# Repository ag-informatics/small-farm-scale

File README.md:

# Welcome to your organization's demo respository
This code repository (or "repo") is designed to demonstrate the best GitHub has to offer with the least amount of noise.

The repo includes an `index.html` file (so it can render a web page), two GitHub Actions workflows, and a CSS stylesheet dependency.

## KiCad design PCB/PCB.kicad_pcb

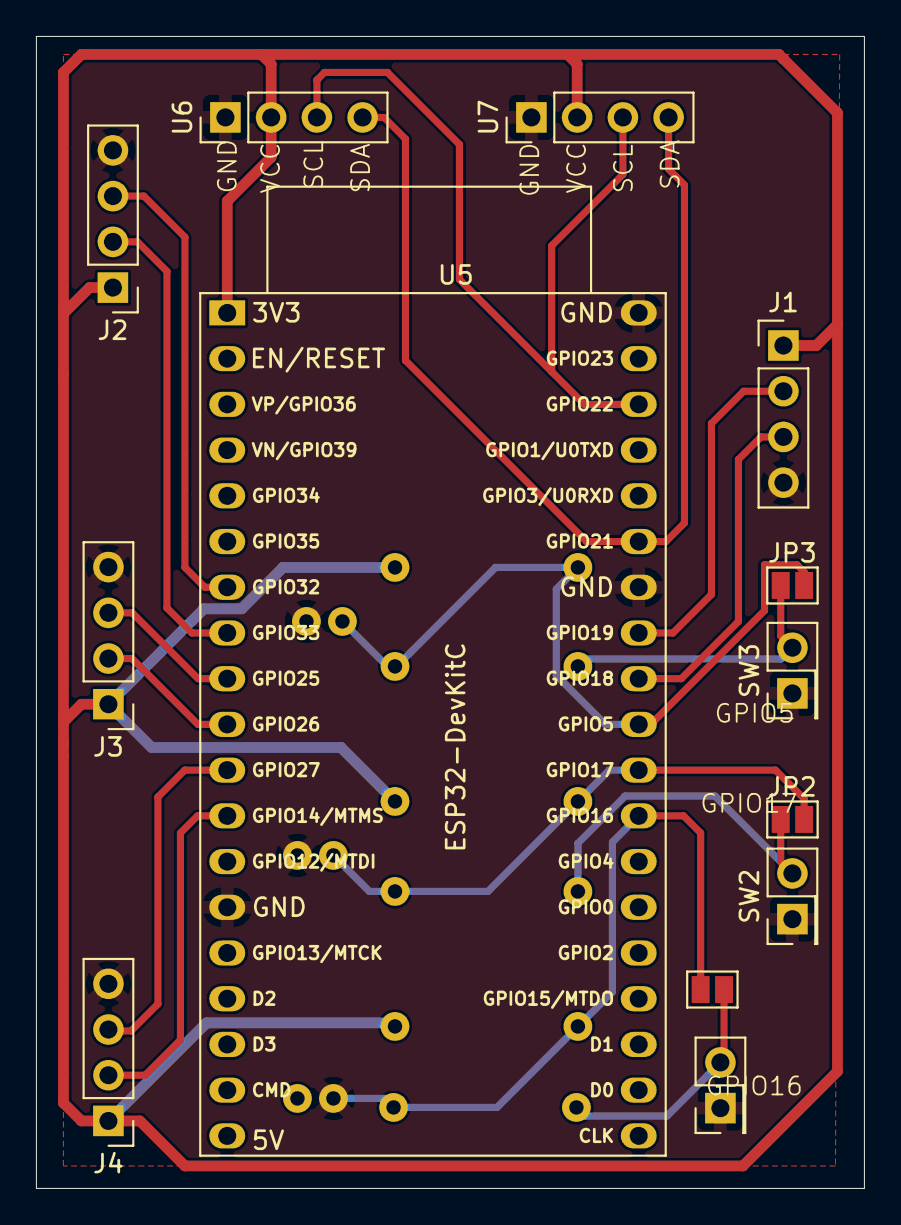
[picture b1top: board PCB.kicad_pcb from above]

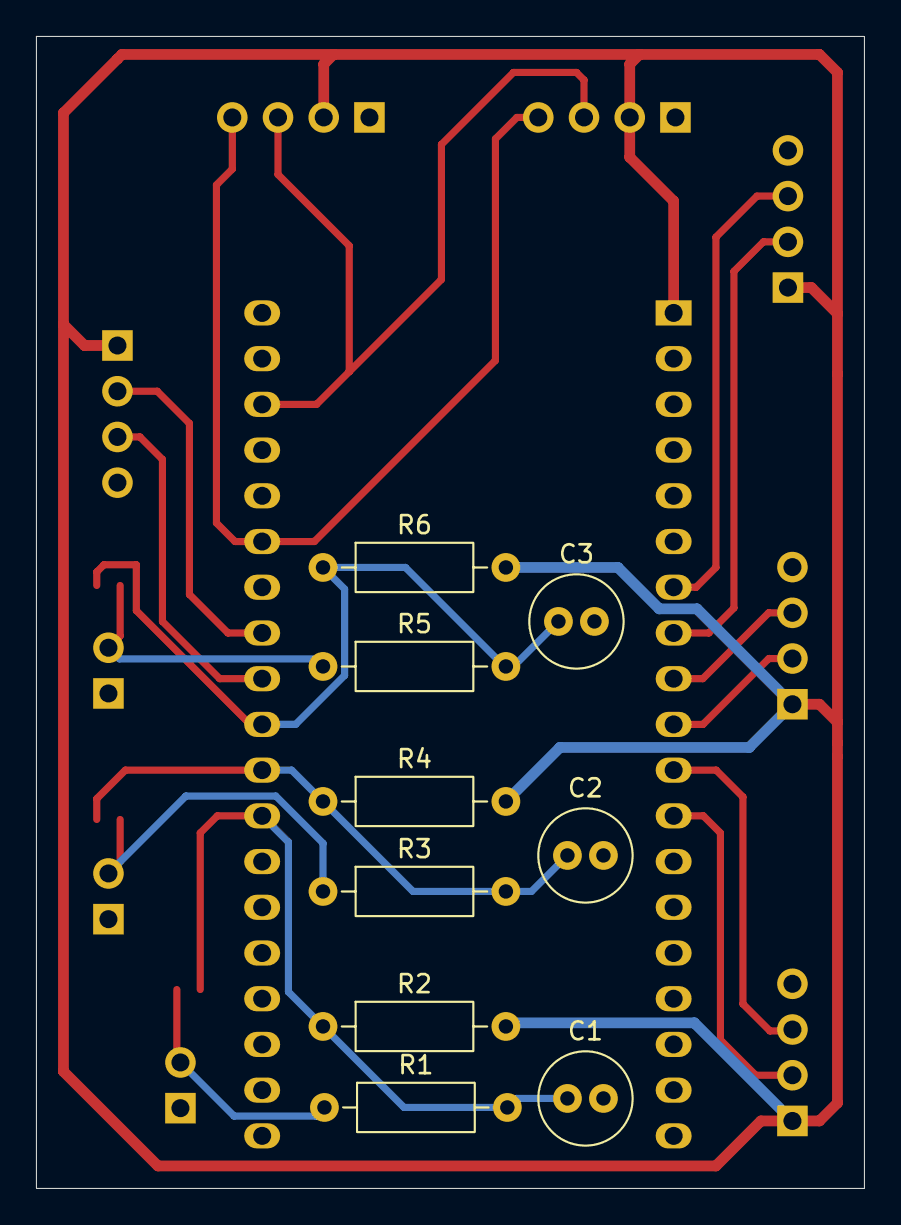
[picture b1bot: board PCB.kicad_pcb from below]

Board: 2 copper layers, 46.0 x 64.0 mm, 22 parts (9 on the bottom side), 18 nets.

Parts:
C1, C2, C3: 0.1uf; C_Radial_D5.0mm_H11.0mm_P2.00mm
J1, J2, J3, J4: Conn_01x04_Socket; PinHeader_1x04_P2.54mm_Vertical
JP1, JP2, JP3: Short this route to use software deboucer; SolderJumper-2_P1.3mm_Open_Pad1.0x1.5mm
R1, R3, R5: 1kΩ; R_Axial_DIN0207_L6.3mm_D2.5mm_P10.16mm_Horizontal
R2, R4, R6: 10kΩ; R_Axial_DIN0207_L6.3mm_D2.5mm_P10.16mm_Horizontal
SW1, SW2, SW3: SW_Push; PinHeader_2x01_P2.54mm_Vertical
U5: ESP32-DevKitC
U6: SD1306; PinHeader_1x04_P2.54mm_Vertical
U7: SD1309; PinHeader_1x04_P2.54mm_Vertical

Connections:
+3.3V: J1.1, J2.1, J3.1, J4.1, R2.2, R4.2, R6.2, U5.1 (3V3), U6.2 (VCC), U7.2 (VCC)
/BTN1: C1.1, JP1.2 (B), R1.2, R2.1, U5.27 (GPIO16)
/BTN2: C2.1, JP2.2 (B), R3.2, R4.1, U5.28 (GPIO17)
/BTN3: C3.1, JP3.2 (B), R5.2, R6.1, U5.29 (GPIO5)
/CLK1: J1.2, U5.31 (GPIO19)
/CLK2: J2.2, U5.8 (32K_XN/GPIO33/ADC1_CH5)
/CLK3: J3.2, U5.10 (DAC_2/ADC2_CH9/GPIO26)
/CLK4: J4.2, U5.12 (MTMS/GPIO14/ADC2_CH6)
/DATA1: J1.3, U5.30 (GPIO18)
/DATA2: J2.3, U5.7 (32K_XP/GPIO32/ADC1_CH4)
/DATA3: J3.3, U5.9 (DAC_1/ADC2_CH8/GPIO25)
/DATA4: J4.3, U5.11 (ADC2_CH7/GPIO27)
GND: C1.2, C2.2, C3.2, J1.4, J2.4, J3.4, J4.4, SW1.1, SW2.1, SW3.1, U5.14 (GND), U5.32 (GND), U5.38 (GND), U6.1 (GND), U7.1 (GND)
unnamed: JP1.1 (A), R1.1, SW1.2
unnamed: JP2.1 (A), R3.1, SW2.2
unnamed: JP3.1 (A), R5.1, SW3.2
unnamed: U5.33 (GPIO21), U6.4 (SDA), U7.4 (SDA)
unnamed: U5.36 (GPIO22), U6.3 (SCL), U7.3 (SCL)

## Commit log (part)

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2026-03-31 first calibration profile
2026-04-02 update calibration profile
2026-04-02 first upload
2026-04-07 Connect to wifi
2026-04-07 Add upload functionality
2026-04-10 Fixed Upload Bug and -0
2026-04-10 Remove auto-assign issues to Ankita
2026-04-13 formatting main file
2026-04-14 separate hx711 functionality
2026-04-14 separate upload function
